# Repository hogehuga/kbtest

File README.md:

# kbtest
自作キーボード記事で作成した基板情報を公開します。
(2022/05/01以降は削除する可能性が高いです)

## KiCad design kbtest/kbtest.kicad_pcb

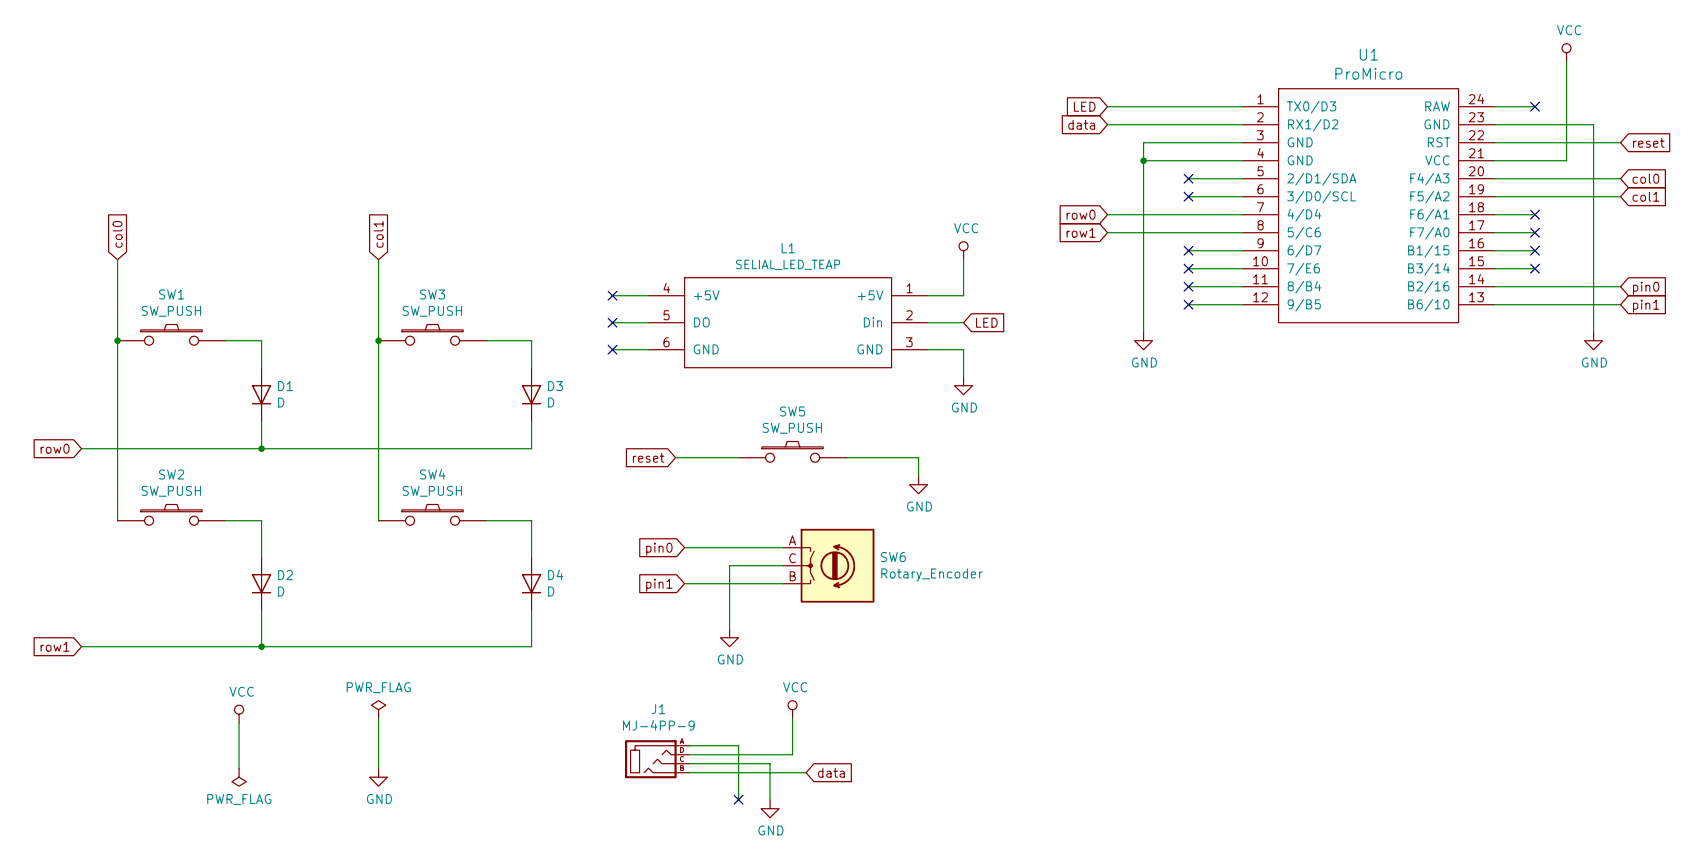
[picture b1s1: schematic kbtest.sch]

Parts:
D1, D2, D3, D4: D; D3_TH
J1: MJ-4PP-9
L1: SELIAL_LED_TEAP; StripLED_1side
SW1, SW2, SW3, SW4: SW_PUSH; CherryMX_1u
SW5: SW_PUSH; ResetSW
SW6: Rotary_Encoder; RotaryEncoder_EC11
U1: ProMicro; ProMicro_v2

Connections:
GND: J1.C, L1.3 (GND), SW5.2, SW6.C, U1.3 (GND), U1.4 (GND), U1.23 (GND)
LED: L1.2 (Din), U1.1 (TX0/D3)
unnamed: D1.2 (A), SW1.2
unnamed: D2.2 (A), SW2.2
unnamed: D3.2 (A), SW3.2
unnamed: D4.2 (A), SW4.2
VCC: J1.D, L1.1 (+5V), U1.21 (VCC)
col0: SW1.1, SW2.1, U1.20 (F4/A3)
col1: SW3.1, SW4.1, U1.19 (F5/A2)
data: J1.B, U1.2 (RX1/D2)
pin0: SW6.A, U1.14 (B2/16)
pin1: SW6.B, U1.13 (B6/10)
reset: SW5.1, U1.22 (RST)
row0: D1.1 (K), D3.1 (K), U1.7 (4/D4)
row1: D2.1 (K), D4.1 (K), U1.8 (5/C6)

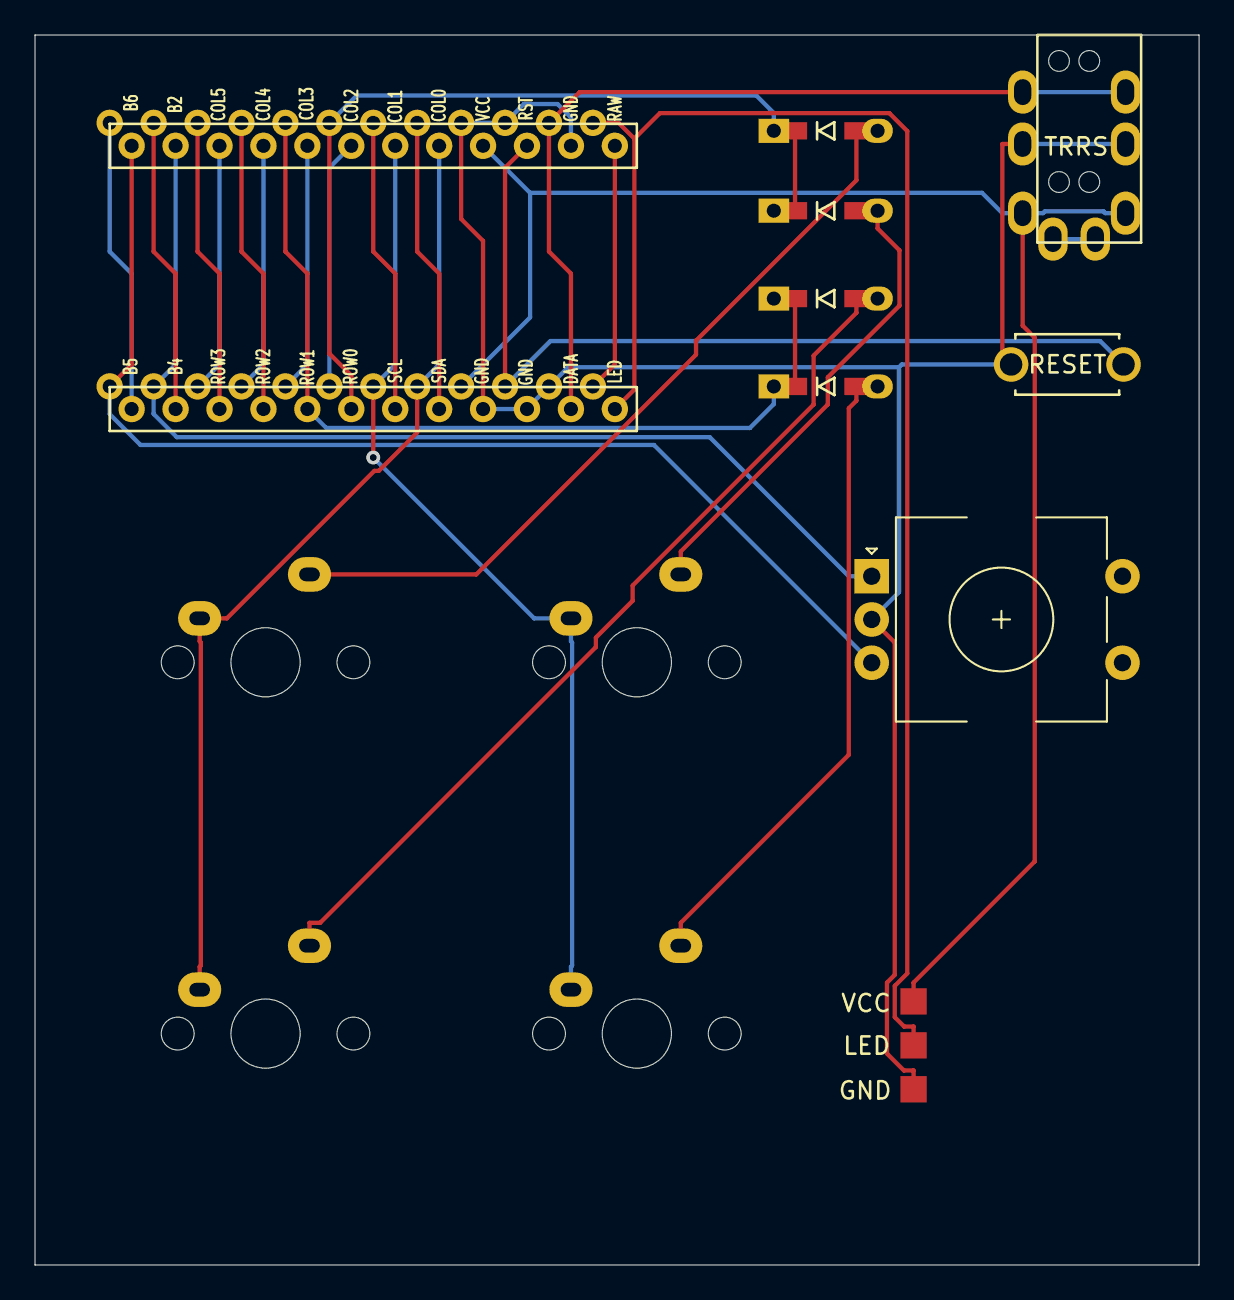
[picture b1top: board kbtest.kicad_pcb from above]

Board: 2 copper layers, 67.3 x 71.1 mm, 13 parts (0 on the bottom side), 15 nets.
